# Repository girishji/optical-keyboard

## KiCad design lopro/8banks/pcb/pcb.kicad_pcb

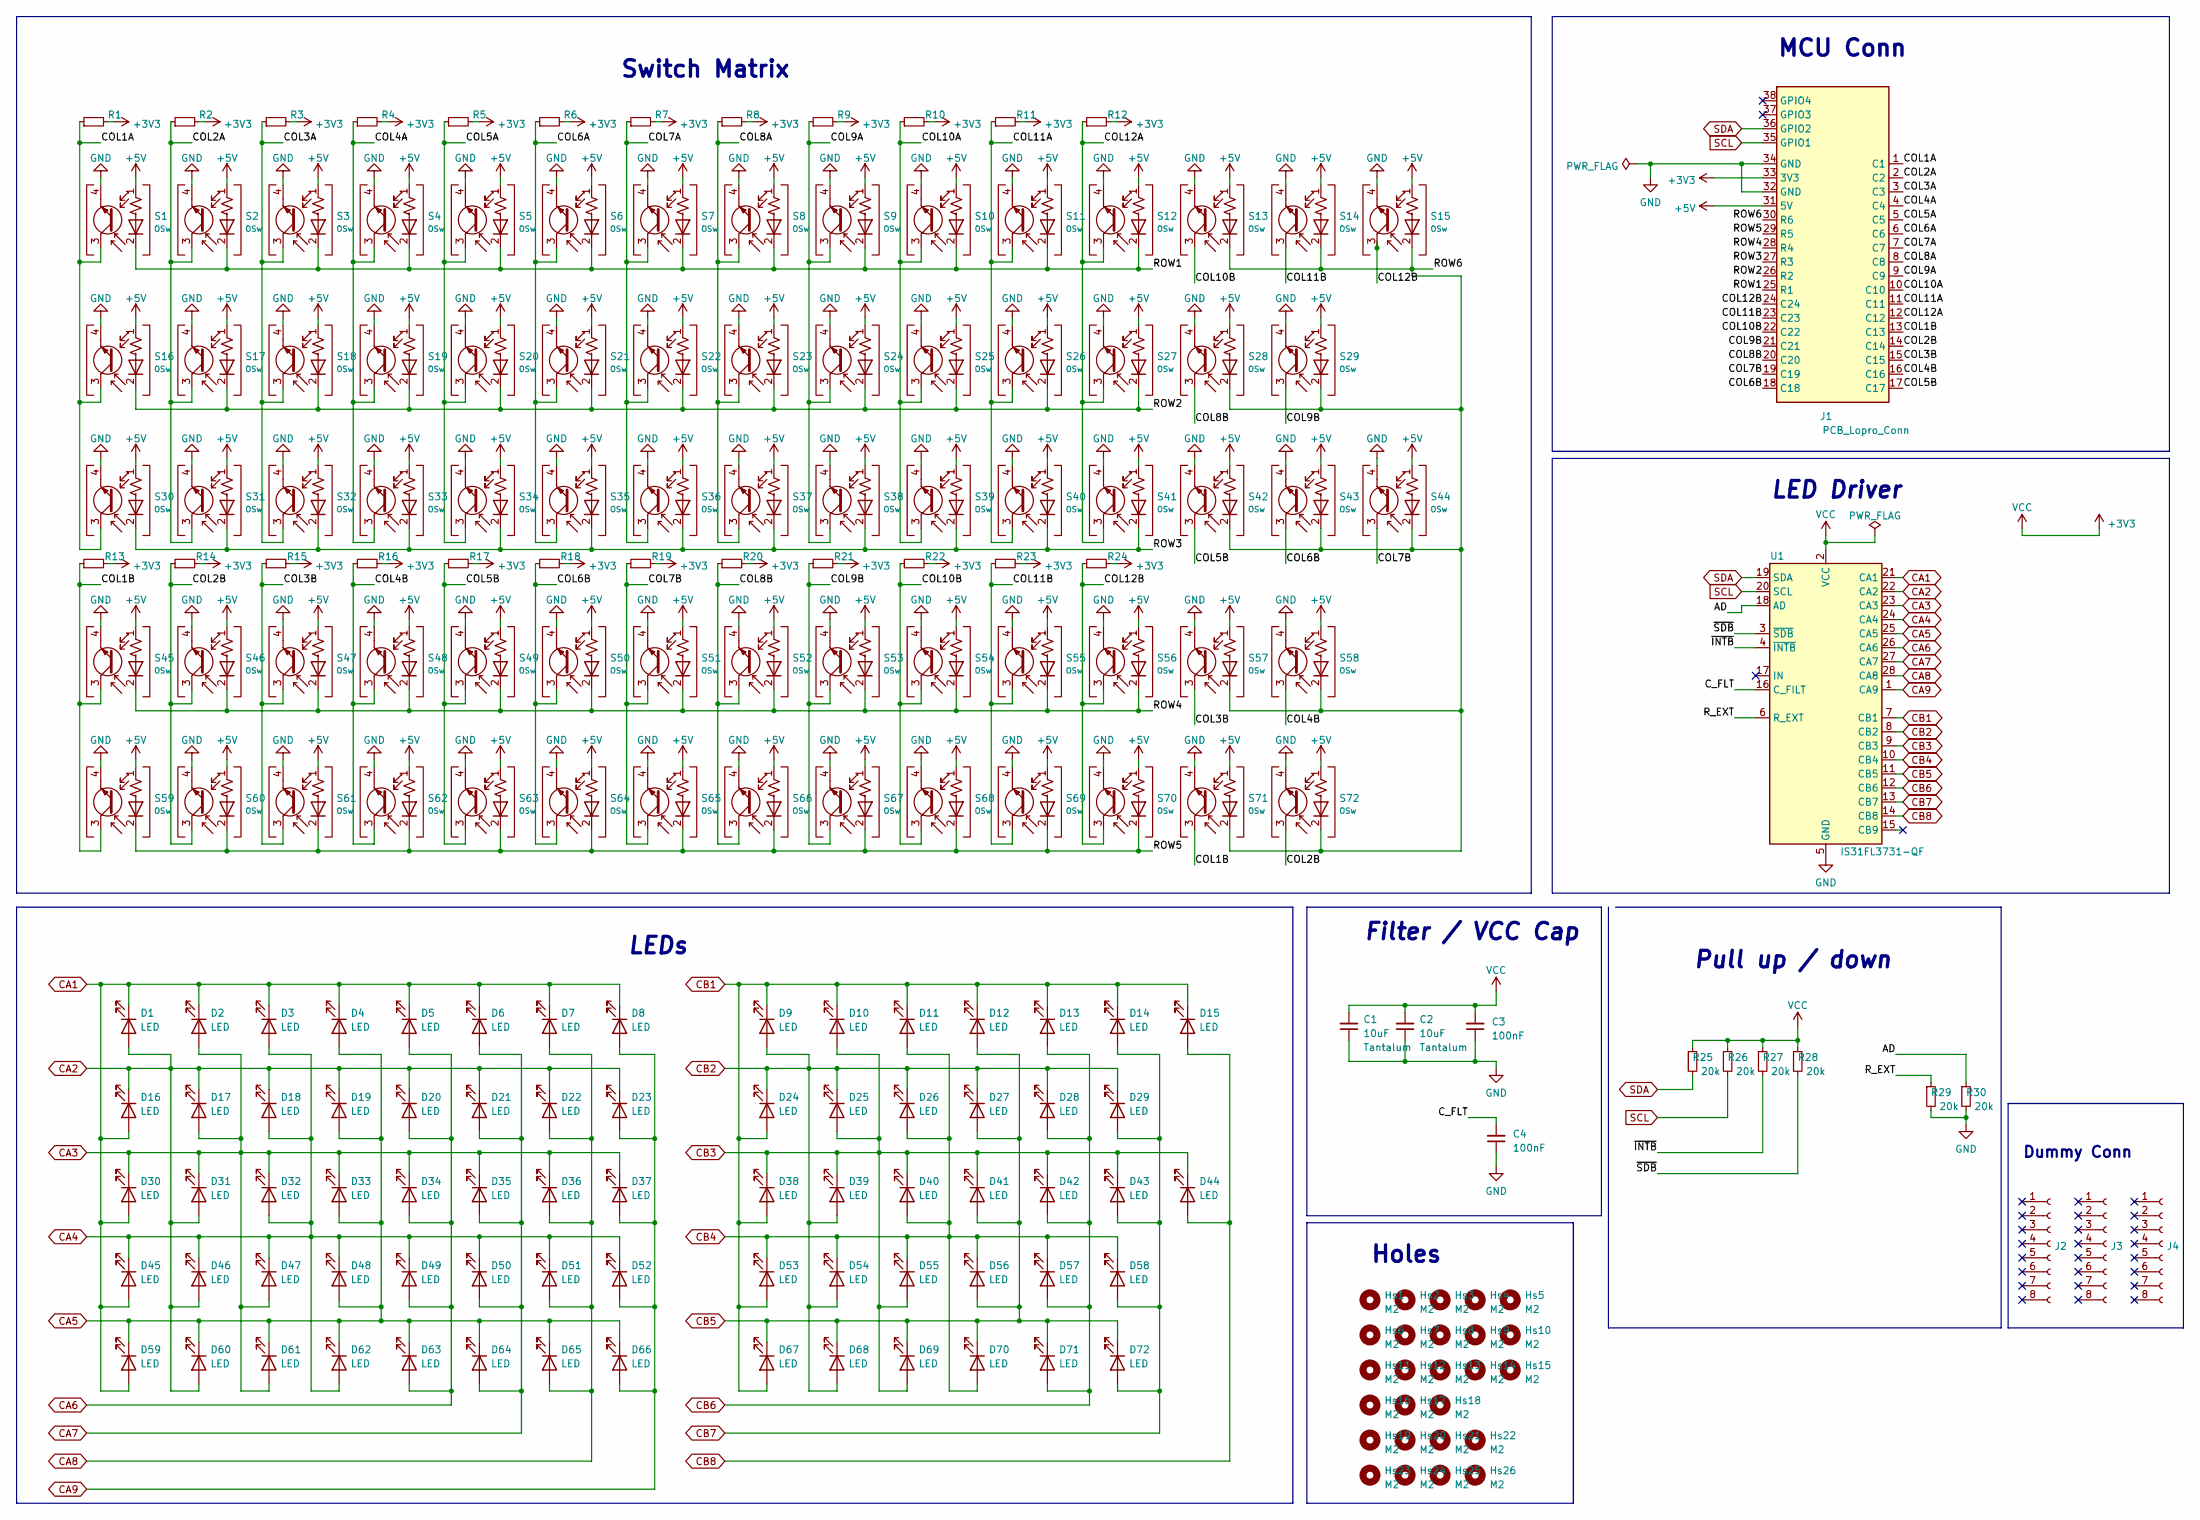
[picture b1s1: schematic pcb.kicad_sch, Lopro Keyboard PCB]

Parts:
C1, C2: 10uF; C_1206_3216Metric; JLC 10uF_tantalum
C3, C4: 100nF; C_0603_1608Metric; JLC smd_100nf
D1, D2, D3, D4, D5, D6, D7, D8, D9, D10, D11, D12, D13, D14, D15, D16, D17, D18, D19, D20, D21, D22, D23, D24, D25, D26, D27, D28, D29, D30, D31, D32, D33, D34, D35, D36, D37, D38, D39, D40, D41, D42, D43, D44, D45, D46, D47, D48, D49, D50, D51, D52, D53, D54, D55, D56, D57, D58, D59, D60, D61, D62, D63, D64, D65, D66, D67, D68, D69, D70, D71, D72: LED; LED_0603_1608Metric_Pad1.05x0.95mm_HandSolder
Hs1, Hs2, Hs3, Hs4, Hs5, Hs6, Hs7, Hs8, Hs9, Hs10, Hs11, Hs12, Hs13, Hs14, Hs15, Hs16, Hs17, Hs18, Hs19, Hs20, Hs21, Hs22, Hs23, Hs24, Hs25, Hs26: M2; SMTSO_M2
J1: PCB_Lopro_Conn; DSUB-37_Female_Horizontal_P2.77x2.84mm_EdgePinOffset4.94mm_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
J2, J3, J4: Conn_01x08_Female; PinHeader_1x08_P2.54mm_Vertical
R1, R2, R3, R4, R5, R6, R7, R8, R9, R10, R11, R12, R13, R14, R15, R16, R17, R18, R19, R20, R21, R22, R23, R24: R_Small; R_0603_1608Metric_Pad0.98x0.95mm_HandSolder
R25, R26, R27, R28, R29, R30: 20k; R_0603_1608Metric; JLC 20k
S1, S2, S3, S4, S5, S6, S7, S8, S9, S10, S11, S12, S13, S14, S15, S16, S17, S18, S19, S20, S21, S22, S23, S24, S25, S26, S27, S28, S29, S30, S31, S32, S33, S34, S35, S36, S37, S38, S39, S40, S41, S42, S43, S44, S45, S46, S47, S48, S49, S50, S51, S52, S53, S54, S55, S56, S57, S58, S59, S60, S61, S62, S63, S64, S65, S66, S67, S68, S69, S70, S71, S72: OSw; Keychron_Optical_Switch_1u
U1: IS31FL3731-QF; QFN-28-1EP_4x4mm_P0.4mm_EP2.3x2.3mm; JLCPCB IS31FL3731-QFLS2-TR

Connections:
+3V3: C1.2, C2.2, C3.2, J1.33 (3V3), R1.2, R2.2, R3.2, R4.2, R5.2, R6.2, R7.2, R8.2, R9.2, R10.2, R11.2, R12.2, R13.2, R14.2, R15.2, R16.2, R17.2, R18.2, R19.2, R20.2, R21.2, R22.2, R23.2, R24.2, R25.1, R26.1, R27.1, R28.1, U1.2 (VCC)
+5V: J1.31 (5V), S1.1 (IR_A), S2.1 (IR_A), S3.1 (IR_A), S4.1 (IR_A), S5.1 (IR_A), S6.1 (IR_A), S7.1 (IR_A), S8.1 (IR_A), S9.1 (IR_A), S10.1 (IR_A), S11.1 (IR_A), S12.1 (IR_A), S13.1 (IR_A), S14.1 (IR_A), S15.1 (IR_A), S16.1 (IR_A), S17.1 (IR_A), S18.1 (IR_A), S19.1 (IR_A), S20.1 (IR_A), S21.1 (IR_A), S22.1 (IR_A), S23.1 (IR_A), S24.1 (IR_A), S25.1 (IR_A), S26.1 (IR_A), S27.1 (IR_A), S28.1 (IR_A), S29.1 (IR_A), S30.1 (IR_A), S31.1 (IR_A), S32.1 (IR_A), S33.1 (IR_A), S34.1 (IR_A), S35.1 (IR_A), S36.1 (IR_A), S37.1 (IR_A), S38.1 (IR_A), S39.1 (IR_A), S40.1 (IR_A), S41.1 (IR_A), S42.1 (IR_A), S43.1 (IR_A), S44.1 (IR_A), S45.1 (IR_A), S46.1 (IR_A), S47.1 (IR_A), S48.1 (IR_A), S49.1 (IR_A), S50.1 (IR_A), S51.1 (IR_A), S52.1 (IR_A), S53.1 (IR_A), S54.1 (IR_A), S55.1 (IR_A), S56.1 (IR_A), S57.1 (IR_A), S58.1 (IR_A), S59.1 (IR_A), S60.1 (IR_A), S61.1 (IR_A), S62.1 (IR_A), S63.1 (IR_A), S64.1 (IR_A), S65.1 (IR_A), S66.1 (IR_A), S67.1 (IR_A), S68.1 (IR_A), S69.1 (IR_A), S70.1 (IR_A), S71.1 (IR_A), S72.1 (IR_A)
/AD: R30.1, U1.18 (AD)
/COL1A: J1.1 (C1), R1.1, S1.3 (C), S16.3 (C), S30.3 (C)
/COL1B: J1.13 (C13), R13.1, S45.3 (C), S59.3 (C), S71.3 (C)
/COL2A: J1.2 (C2), R2.1, S2.3 (C), S17.3 (C), S31.3 (C)
/COL2B: J1.14 (C14), R14.1, S46.3 (C), S60.3 (C), S72.3 (C)
/COL3A: J1.3 (C3), R3.1, S3.3 (C), S18.3 (C), S32.3 (C)
/COL3B: J1.15 (C15), R15.1, S47.3 (C), S57.3 (C), S61.3 (C)
/COL4A: J1.4 (C4), R4.1, S4.3 (C), S19.3 (C), S33.3 (C)
/COL4B: J1.16 (C16), R16.1, S48.3 (C), S58.3 (C), S62.3 (C)
/COL5A: J1.5 (C5), R5.1, S5.3 (C), S20.3 (C), S34.3 (C)
/COL5B: J1.17 (C17), R17.1, S42.3 (C), S49.3 (C), S63.3 (C)
/COL6A: J1.6 (C6), R6.1, S6.3 (C), S21.3 (C), S35.3 (C)
/COL6B: J1.18 (C18), R18.1, S43.3 (C), S50.3 (C), S64.3 (C)
/COL7A: J1.7 (C7), R7.1, S7.3 (C), S22.3 (C), S36.3 (C)
/COL7B: J1.19 (C19), R19.1, S44.3 (C), S51.3 (C), S65.3 (C)
/COL8A: J1.8 (C8), R8.1, S8.3 (C), S23.3 (C), S37.3 (C)
/COL8B: J1.20 (C20), R20.1, S28.3 (C), S52.3 (C), S66.3 (C)
/COL9A: J1.9 (C9), R9.1, S9.3 (C), S24.3 (C), S38.3 (C)
/COL9B: J1.21 (C21), R21.1, S29.3 (C), S53.3 (C), S67.3 (C)
/COL10A: J1.10 (C10), R10.1, S10.3 (C), S25.3 (C), S39.3 (C)
/COL10B: J1.22 (C22), R22.1, S13.3 (C), S54.3 (C), S68.3 (C)
/COL11A: J1.11 (C11), R11.1, S11.3 (C), S26.3 (C), S40.3 (C)
/COL11B: J1.23 (C23), R23.1, S14.3 (C), S55.3 (C), S69.3 (C)
/COL12A: J1.12 (C12), R12.1, S12.3 (C), S27.3 (C), S41.3 (C)
/COL12B: J1.24 (C24), R24.1, S15.3 (C), S56.3 (C), S70.3 (C)
/C_FLT: C4.2, U1.16 (C_FILT)
/ROW1: J1.25 (R1), S1.2 (IR_K), S2.2 (IR_K), S3.2 (IR_K), S4.2 (IR_K), S5.2 (IR_K), S6.2 (IR_K), S7.2 (IR_K), S8.2 (IR_K), S9.2 (IR_K), S10.2 (IR_K), S11.2 (IR_K), S12.2 (IR_K)
/ROW2: J1.26 (R2), S16.2 (IR_K), S17.2 (IR_K), S18.2 (IR_K), S19.2 (IR_K), S20.2 (IR_K), S21.2 (IR_K), S22.2 (IR_K), S23.2 (IR_K), S24.2 (IR_K), S25.2 (IR_K), S26.2 (IR_K), S27.2 (IR_K)
/ROW3: J1.27 (R3), S30.2 (IR_K), S31.2 (IR_K), S32.2 (IR_K), S33.2 (IR_K), S34.2 (IR_K), S35.2 (IR_K), S36.2 (IR_K), S37.2 (IR_K), S38.2 (IR_K), S39.2 (IR_K), S40.2 (IR_K), S41.2 (IR_K)
/ROW4: J1.28 (R4), S45.2 (IR_K), S46.2 (IR_K), S47.2 (IR_K), S48.2 (IR_K), S49.2 (IR_K), S50.2 (IR_K), S51.2 (IR_K), S52.2 (IR_K), S53.2 (IR_K), S54.2 (IR_K), S55.2 (IR_K), S56.2 (IR_K)
/ROW5: J1.29 (R5), S59.2 (IR_K), S60.2 (IR_K), S61.2 (IR_K), S62.2 (IR_K), S63.2 (IR_K), S64.2 (IR_K), S65.2 (IR_K), S66.2 (IR_K), S67.2 (IR_K), S68.2 (IR_K), S69.2 (IR_K), S70.2 (IR_K)
/ROW6: J1.30 (R6), S13.2 (IR_K), S14.2 (IR_K), S15.2 (IR_K), S28.2 (IR_K), S29.2 (IR_K), S42.2 (IR_K), S43.2 (IR_K), S44.2 (IR_K), S57.2 (IR_K), S58.2 (IR_K), S71.2 (IR_K), S72.2 (IR_K)
/R_EXT: R29.1, U1.6 (R_EXT)
/~INTB: R27.2, U1.4 (~INTB)
/~SDB: R28.2, U1.3 (~SDB)
CA1: D1.1 (K), D2.1 (K), D3.1 (K), D4.1 (K), D5.1 (K), D6.1 (K), D7.1 (K), D8.1 (K), D16.2 (A), D30.2 (A), D45.2 (A), D59.2 (A), U1.21 (CA1)
CA2: D1.2 (A), D16.1 (K), D17.1 (K), D18.1 (K), D19.1 (K), D20.1 (K), D21.1 (K), D22.1 (K), D23.1 (K), D31.2 (A), D46.2 (A), D60.2 (A), U1.22 (CA2)
CA3: D2.2 (A), D17.2 (A), D30.1 (K), D31.1 (K), D32.1 (K), D33.1 (K), D34.1 (K), D35.1 (K), D36.1 (K), D37.1 (K), D47.2 (A), D61.2 (A), U1.23 (CA3)
CA4: D3.2 (A), D18.2 (A), D32.2 (A), D45.1 (K), D46.1 (K), D47.1 (K), D48.1 (K), D49.1 (K), D50.1 (K), D51.1 (K), D52.1 (K), D62.2 (A), U1.24 (CA4)
CA5: D4.2 (A), D19.2 (A), D33.2 (A), D48.2 (A), D59.1 (K), D60.1 (K), D61.1 (K), D62.1 (K), D63.1 (K), D64.1 (K), D65.1 (K), D66.1 (K), U1.25 (CA5)
CA6: D5.2 (A), D20.2 (A), D34.2 (A), D49.2 (A), D63.2 (A), U1.26 (CA6)
CA7: D6.2 (A), D21.2 (A), D35.2 (A), D50.2 (A), D64.2 (A), U1.27 (CA7)
CA8: D7.2 (A), D22.2 (A), D36.2 (A), D51.2 (A), D65.2 (A), U1.28 (CA8)
CA9: D8.2 (A), D23.2 (A), D37.2 (A), D52.2 (A), D66.2 (A), U1.1 (CA9)
CB1: D9.1 (K), D10.1 (K), D11.1 (K), D12.1 (K), D13.1 (K), D14.1 (K), D15.1 (K), D24.2 (A), D38.2 (A), D53.2 (A), D67.2 (A), U1.7 (CB1)
CB2: D9.2 (A), D24.1 (K), D25.1 (K), D26.1 (K), D27.1 (K), D28.1 (K), D29.1 (K), D39.2 (A), D54.2 (A), D68.2 (A), U1.8 (CB2)
CB3: D10.2 (A), D25.2 (A), D38.1 (K), D39.1 (K), D40.1 (K), D41.1 (K), D42.1 (K), D43.1 (K), D44.1 (K), D55.2 (A), D69.2 (A), U1.9 (CB3)
CB4: D11.2 (A), D26.2 (A), D40.2 (A), D53.1 (K), D54.1 (K), D55.1 (K), D56.1 (K), D57.1 (K), D58.1 (K), D70.2 (A), U1.10 (CB4)
CB5: D12.2 (A), D27.2 (A), D41.2 (A), D56.2 (A), D67.1 (K), D68.1 (K), D69.1 (K), D70.1 (K), D71.1 (K), D72.1 (K), U1.11 (CB5)
CB6: D13.2 (A), D28.2 (A), D42.2 (A), D57.2 (A), D71.2 (A), U1.12 (CB6)
CB7: D14.2 (A), D29.2 (A), D43.2 (A), D58.2 (A), D72.2 (A), U1.13 (CB7)
CB8: D15.2 (A), D44.2 (A), U1.14 (CB8)
GND: C1.1, C2.1, C3.1, C4.1, J1.32 (GND), J1.34 (GND), R29.2, R30.2, S1.4 (E), S2.4 (E), S3.4 (E), S4.4 (E), S5.4 (E), S6.4 (E), S7.4 (E), S8.4 (E), S9.4 (E), S10.4 (E), S11.4 (E), S12.4 (E), S13.4 (E), S14.4 (E), S15.4 (E), S16.4 (E), S17.4 (E), S18.4 (E), S19.4 (E), S20.4 (E), S21.4 (E), S22.4 (E), S23.4 (E), S24.4 (E), S25.4 (E), S26.4 (E), S27.4 (E), S28.4 (E), S29.4 (E), S30.4 (E), S31.4 (E), S32.4 (E), S33.4 (E), S34.4 (E), S35.4 (E), S36.4 (E), S37.4 (E), S38.4 (E), S39.4 (E), S40.4 (E), S41.4 (E), S42.4 (E), S43.4 (E), S44.4 (E), S45.4 (E), S46.4 (E), S47.4 (E), S48.4 (E), S49.4 (E), S50.4 (E), S51.4 (E), S52.4 (E), S53.4 (E), S54.4 (E), S55.4 (E), S56.4 (E), S57.4 (E), S58.4 (E), S59.4 (E), S60.4 (E), S61.4 (E), S62.4 (E), S63.4 (E), S64.4 (E), S65.4 (E), S66.4 (E), S67.4 (E), S68.4 (E), S69.4 (E), S70.4 (E), S71.4 (E), S72.4 (E), U1.5 (GND), U1.29 (GND)
SCL: J1.35 (GPIO1), R26.2, U1.20 (SCL)
SDA: J1.36 (GPIO2), R25.2, U1.19 (SDA)

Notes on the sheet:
Holes
LED Driver
LEDs
Switch Matrix
Dummy Conn
Pull up / down
Filter / VCC Cap
MCU Conn

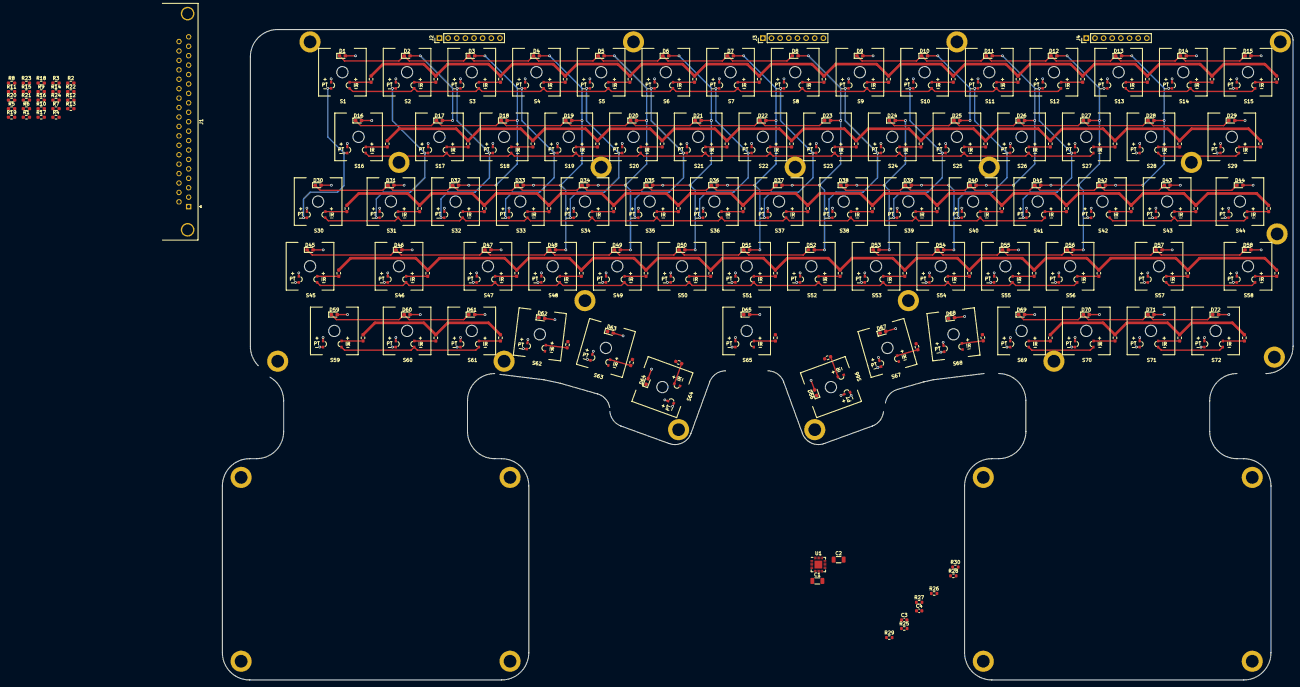
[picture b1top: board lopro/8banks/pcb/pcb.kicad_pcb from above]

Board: 2 copper layers, 314.5 x 191.1 mm, 209 parts (0 on the bottom side), 57 nets.

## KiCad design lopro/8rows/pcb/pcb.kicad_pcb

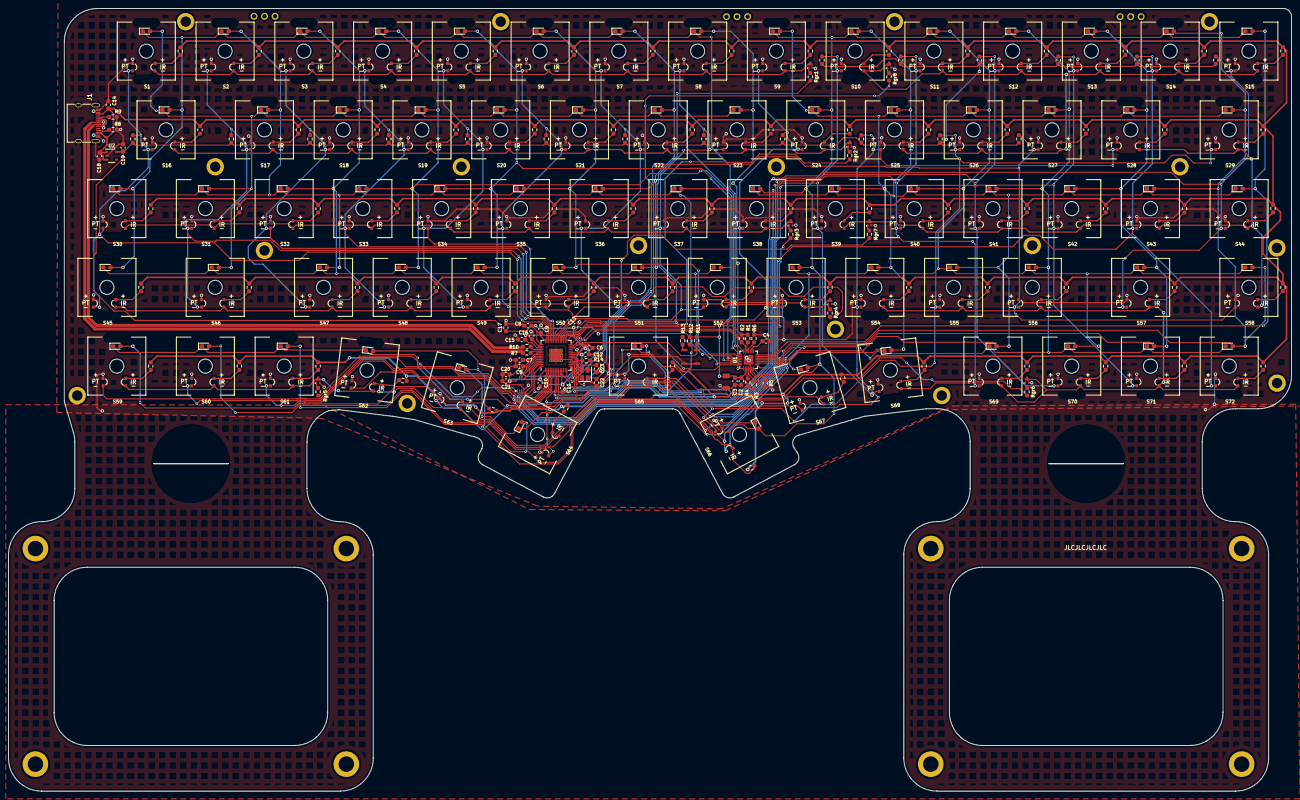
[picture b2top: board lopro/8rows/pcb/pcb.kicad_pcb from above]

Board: 2 copper layers, 309.5 x 188.8 mm, 324 parts (0 on the bottom side), 159 nets.

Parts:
C1: 10uF; C_1206_3216Metric
C2, C17: 10uF; C_0603_1608Metric_Pad1.08x0.95mm_HandSolder
C3, C4, C5, C6, C7, C8, C9, C10, C11, C12, C13, C20: 100nF; C_0603_1608Metric_Pad1.08x0.95mm_HandSolder
C14, C18, C21: 2.2uF; C_0603_1608Metric_Pad1.08x0.95mm_HandSolder
C15, C16, C19: 1uF; C_0603_1608Metric_Pad1.08x0.95mm_HandSolder
C22, C23: 15pF; C_0603_1608Metric_Pad1.08x0.95mm_HandSolder
D1, D2, D3, D4, D5, D6, D7, D8, D9, D10, D11, D12, D13, D14, D15, D16, D17, D18, D19, D20, D21, D22, D23, D24, D25, D26, D27, D28, D29, D30, D31, D32, D33, D34, D35, D36, D37, D38, D39, D40, D41, D42, D43, D44, D45, D46, D47, D48, D49, D50, D51, D52, D53, D54, D55, D56, D57, D58, D59, D60, D61, D62, D63, D64, D65, D66, D67, D68, D69, D70, D71, D72: LED; LED_0603_1608Metric_Pad1.05x0.95mm_HandSolder
Hs1, Hs2, Hs3, Hs4, Hs5, Hs6, Hs7, Hs8, Hs9, Hs10, Hs11, Hs12, Hs13, Hs14, Hs15, Hs16, Hs17: M1.6; SMTSO_M1.6
Hs18, Hs19, Hs20, Hs21, Hs22, Hs23, Hs24, Hs25: M2; SMTSO_M2
J1: U262-161N-4BVC11; USB_C_Receptacle_XKB_U262-16XN-4BVC11
J2, J3, J4: Conn_01x03; PinHeader_1x03_P2.54mm_Vertical
JLC1: JLC_Order_Num
Q1, Q2, Q3, Q4, Q5, Q6, Q7, Q8: Q_NMOS_DGS; Diodes_U_DFN1212_3_Handsolder
R1, R2, R3: 4.7k; R_0603_1608Metric_Pad0.98x0.95mm_HandSolder
R4, R5, R6: 20k; R_0603_1608Metric_Pad0.98x0.95mm_HandSolder
R7, R10: 27R; R_0603_1608Metric_Pad0.98x0.95mm_HandSolder
R8, R9: 5.1k; R_0603_1608Metric_Pad0.98x0.95mm_HandSolder
R11, R12: 10k; R_0603_1608Metric_Pad0.98x0.95mm_HandSolder
R13, R14: 1k; R_0603_1608Metric_Pad0.98x0.95mm_HandSolder
Rgr1, Rgr2, Rgr3, Rgr4, Rgr5, Rgr6, Rgr7, Rgr8: 160R; R_0603_1608Metric_Pad0.98x0.95mm_HandSolder
Ri1, Ri2, Ri3, Ri4, Ri5, Ri6, Ri7, Ri8, Ri9, Ri10, Ri11, Ri12, Ri13, Ri14, Ri15, Ri16, Ri17, Ri18, Ri19, Ri20, Ri21, Ri22, Ri23, Ri24, Ri25, Ri26, Ri27, Ri28, Ri29, Ri30, Ri31, Ri32, Ri33, Ri34, Ri35, Ri36, Ri37, Ri38, Ri39, Ri40, Ri41, Ri42, Ri43, Ri44, Ri45, Ri46, Ri47, Ri48, Ri49, Ri50, Ri51, Ri52, Ri53, Ri54, Ri55, Ri56, Ri57, Ri58, Ri59, Ri60, Ri61, Ri62, Ri63, Ri64, Ri65, Ri66, Ri67, Ri68, Ri69, Ri70, Ri71, Ri72: R_IR; R_0603_1608Metric_Pad0.98x0.95mm_HandSolder
Rpt1, Rpt2, Rpt3, Rpt4, Rpt5, Rpt6, Rpt7, Rpt8, Rpt9, Rpt10, Rpt11, Rpt12, Rpt13, Rpt14, Rpt15, Rpt16, Rpt17, Rpt18: Rpt; R_0603_1608Metric_Pad0.98x0.95mm_HandSolder
S1, S2, S3, S4, S5, S6, S7, S8, S9, S10, S11, S12, S13, S14, S15, S16, S17, S18, S19, S20, S21, S22, S23, S24, S25, S26, S27, S28, S29, S30, S31, S32, S33, S34, S35, S36, S37, S38, S39, S40, S41, S42, S43, S44, S45, S46, S47, S48, S49, S50, S51, S52, S53, S54, S55, S56, S57, S58, S59, S60, S61, S62, S63, S64, S65, S66, S67, S68, S69, S70, S71, S72: OSw; Keychron_Optical_Switch_1u
SW1, SW2: SW_DIP_x01_XKB_TS_2030; SW_CK_KXT3
U1: IS31FL3731-QF; QFN-28-1EP_4x4mm_P0.4mm_EP2.3x2.3mm-Handsolder
U2: NCP114ASN330T1G; TSOP-5_1.65x3.05mm_P0.95mm
U3: RP2040; RP2040-QFN-56-Handsolder
U4: Memory_Flash_W25Q64_XSON; 8-USON-Handsolder
X1: 12.000MHz; Crystal_SMD_2520-4Pin_2.5x2.0mm-Handsolder

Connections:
+1V1: C5.1, C6.1, C15.1, U3.23 (DVDD), U3.45 (VREG_VOUT), U3.50 (DVDD)
+3V3: C1.2, C2.1, C3.1, C7.1, C8.1, C9.1, C10.1, C11.1, C12.1, C13.1, C16.1, C17.1, C19.1, C20.1, C21.1, R1.1, R2.1, R3.1, R4.1, R11.1, R12.1, Rpt1.2, Rpt2.2, Rpt3.2, Rpt4.2, Rpt5.2, Rpt6.2, Rpt7.2, Rpt8.2, Rpt9.2, Rpt10.2, Rpt11.2, Rpt12.2, Rpt13.2, Rpt14.2, Rpt15.2, Rpt16.2, Rpt17.2, Rpt18.2, U1.2 (VCC), U2.5 (VOUT), U3.1 (IOVDD), U3.10 (IOVDD), U3.22 (IOVDD), U3.33 (IOVDD), U3.42 (IOVDD), U3.43 (ADC_AVDD), U3.44 (VREG_IN), U3.48 (USB_VDD), U3.49 (IOVDD), U4.8 (VCC)
+5V: C14.2, C18.1, J1.A4 (VBUS), J1.A9 (VBUS), J1.B4 (VBUS), J1.B9 (VBUS), Ri1.1, Ri2.1, Ri3.1, Ri4.1, Ri5.1, Ri6.1, Ri7.1, Ri8.1, Ri9.1, Ri10.1, Ri11.1, Ri12.1, Ri13.1, Ri14.1, Ri15.1, Ri16.1, Ri17.1, Ri18.1, Ri19.1, Ri20.1, Ri21.1, Ri22.1, Ri23.1, Ri24.1, Ri25.1, Ri26.1, Ri27.1, Ri28.1, Ri29.1, Ri30.1, Ri31.1, Ri32.1, Ri33.1, Ri34.1, Ri35.1, Ri36.1, Ri37.1, Ri38.1, Ri39.1, Ri40.1, Ri41.1, Ri42.1, Ri43.1, Ri44.1, Ri45.1, Ri46.1, Ri47.1, Ri48.1, Ri49.1, Ri50.1, Ri51.1, Ri52.1, Ri53.1, Ri54.1, Ri55.1, Ri56.1, Ri57.1, Ri58.1, Ri59.1, Ri60.1, Ri61.1, Ri62.1, Ri63.1, Ri64.1, Ri65.1, Ri66.1, Ri67.1, Ri68.1, Ri69.1, Ri70.1, Ri71.1, Ri72.1, U2.1 (IN), U2.3 (EN)
/AD: R6.1, U1.18 (AD)
/COL1A: Rpt1.1, S1.3 (C), S16.3 (C), S30.3 (C), S45.3 (C), U3.41 (GPIO29_ADC3)
/COL1B: Rpt10.1, S10.3 (C), S39.3 (C), S59.3 (C), S68.3 (C), U3.2 (GPIO0)
/COL2A: Rpt2.1, S2.3 (C), S17.3 (C), S31.3 (C), S46.3 (C), U3.40 (GPIO28_ADC2)
/COL2B: Rpt11.1, S11.3 (C), S40.3 (C), S60.3 (C), S69.3 (C), U3.3 (GPIO1)
/COL3A: Rpt3.1, S3.3 (C), S18.3 (C), S32.3 (C), S47.3 (C), U3.39 (GPIO27_ADC1)
/COL3B: Rpt12.1, S12.3 (C), S41.3 (C), S61.3 (C), S70.3 (C), U3.4 (GPIO2)
/COL4A: Rpt4.1, S4.3 (C), S19.3 (C), S33.3 (C), S48.3 (C), U3.38 (GPIO26_ADC0)
/COL4B: Rpt13.1, S13.3 (C), S42.3 (C), S62.3 (C), S71.3 (C), U3.5 (GPIO3)
/COL5A: Rpt5.1, S5.3 (C), S20.3 (C), S34.3 (C), S49.3 (C), U3.37 (GPIO25)
/COL5B: Rpt14.1, S14.3 (C), S43.3 (C), S63.3 (C), S72.3 (C), U3.6 (GPIO4)
/COL6A: Rpt6.1, S6.3 (C), S21.3 (C), S35.3 (C), S50.3 (C), U3.36 (GPIO24)
/COL6B: Rpt15.1, S15.3 (C), S44.3 (C), S57.3 (C), S64.3 (C), U3.7 (GPIO5)
/COL7A: Rpt7.1, S7.3 (C), S22.3 (C), S36.3 (C), S51.3 (C), U3.35 (GPIO23)
/COL7B: Rpt16.1, S27.3 (C), S56.3 (C), S58.3 (C), S65.3 (C), U3.8 (GPIO6)
/COL8A: Rpt8.1, S8.3 (C), S23.3 (C), S37.3 (C), S52.3 (C), U3.34 (GPIO22)
/COL8B: Rpt17.1, S26.3 (C), S29.3 (C), S55.3 (C), S66.3 (C), U3.9 (GPIO7)
/COL9A: Rpt9.1, S9.3 (C), S24.3 (C), S38.3 (C), S53.3 (C), U3.32 (GPIO21)
/COL9B: Rpt18.1, S25.3 (C), S28.3 (C), S54.3 (C), S67.3 (C), U3.11 (GPIO8)
/C_FLT: C4.1, U1.16 (C_FILT)
/P1: Rgr1.1, U3.31 (GPIO20)
/P2: Rgr2.1, U3.30 (GPIO19)
/P3: Rgr3.1, U3.29 (GPIO18)
/P4: Rgr4.1, U3.18 (GPIO15)
/P5: Rgr5.1, U3.17 (GPIO14)
/P6: Rgr6.1, U3.16 (GPIO13)
/P7: Rgr7.1, U3.15 (GPIO12)
/P8: Rgr8.1, U3.14 (GPIO11)
/QSPI_SCLK: U3.52 (QSPI_SCLK), U4.6 (CLK)
/QSPI_SD0: U3.53 (QSPI_SD0), U4.5 (DI_(IO0))
/QSPI_SD1: U3.55 (QSPI_SD1), U4.2 (DO_(IO1))
/QSPI_SD2: U3.54 (QSPI_SD2), U4.3 (~WP_(IO2))
/QSPI_SD3: U3.51 (QSPI_SD3), U4.7 (~HOLD_(IO3))
/QSPI_SS: R12.2, R13.1, U3.56 (QSPI_SS), U4.1 (~{CS)
/ROW1: Q1.1 (D), S1.2 (IR_K), S2.2 (IR_K), S3.2 (IR_K), S4.2 (IR_K), S5.2 (IR_K), S6.2 (IR_K), S7.2 (IR_K), S8.2 (IR_K), S9.2 (IR_K)
/ROW2: Q2.1 (D), S16.2 (IR_K), S17.2 (IR_K), S18.2 (IR_K), S19.2 (IR_K), S20.2 (IR_K), S21.2 (IR_K), S22.2 (IR_K), S23.2 (IR_K), S24.2 (IR_K)
/ROW3: Q3.1 (D), S30.2 (IR_K), S31.2 (IR_K), S32.2 (IR_K), S33.2 (IR_K), S34.2 (IR_K), S35.2 (IR_K), S36.2 (IR_K), S37.2 (IR_K), S38.2 (IR_K)
/ROW4: Q4.1 (D), S45.2 (IR_K), S46.2 (IR_K), S47.2 (IR_K), S48.2 (IR_K), S49.2 (IR_K), S50.2 (IR_K), S51.2 (IR_K), S52.2 (IR_K), S53.2 (IR_K)
/ROW5: Q5.1 (D), S59.2 (IR_K), S60.2 (IR_K), S61.2 (IR_K), S62.2 (IR_K), S63.2 (IR_K), S64.2 (IR_K), S65.2 (IR_K), S66.2 (IR_K), S67.2 (IR_K)
/ROW6: Q6.1 (D), S54.2 (IR_K), S55.2 (IR_K), S56.2 (IR_K), S57.2 (IR_K), S68.2 (IR_K), S69.2 (IR_K), S70.2 (IR_K), S71.2 (IR_K), S72.2 (IR_K)
/ROW7: Q7.1 (D), S28.2 (IR_K), S29.2 (IR_K), S39.2 (IR_K), S40.2 (IR_K), S41.2 (IR_K), S42.2 (IR_K), S43.2 (IR_K), S44.2 (IR_K), S58.2 (IR_K)
/ROW8: Q8.1 (D), S10.2 (IR_K), S11.2 (IR_K), S12.2 (IR_K), S13.2 (IR_K), S14.2 (IR_K), S15.2 (IR_K), S25.2 (IR_K), S26.2 (IR_K), S27.2 (IR_K)
/RUN: R11.2, SW1.2, U3.26 (RUN)
/R_EXT: R5.1, U1.6 (R_EXT)
/USB_D+: J1.A6 (D1+), J1.B6 (D2+), R7.2
/USB_D-: J1.A7 (D1-), J1.B7 (D2-), R10.2
/XIN: C23.1, U3.20 (XIN), X1.3
/XOUT: R14.1, U3.21 (XOUT)
/~INTB: R3.2, U1.4 (~INTB)
/~SDB: R4.2, U1.3 (~SDB)
/~USB_BOOT: R13.2, SW2.2
CA1: D1.1 (K), D2.1 (K), D3.1 (K), D4.1 (K), D5.1 (K), D6.1 (K), D7.1 (K), D8.1 (K), D16.2 (A), D30.2 (A), D45.2 (A), U1.21 (CA1)
CA2: D1.2 (A), D16.1 (K), D17.1 (K), D18.1 (K), D19.1 (K), D20.1 (K), D21.1 (K), D22.1 (K), D23.1 (K), D31.2 (A), D46.2 (A), U1.22 (CA2)
CA3: D2.2 (A), D17.2 (A), D30.1 (K), D31.1 (K), D32.1 (K), D33.1 (K), D34.1 (K), D35.1 (K), D36.1 (K), D37.1 (K), D47.2 (A), U1.23 (CA3)
CA4: D3.2 (A), D18.2 (A), D32.2 (A), D45.1 (K), D46.1 (K), D47.1 (K), D48.1 (K), D49.1 (K), D50.1 (K), D51.1 (K), D52.1 (K), U1.24 (CA4)
CA5: D4.2 (A), D19.2 (A), D33.2 (A), D48.2 (A), U1.25 (CA5)
CA6: D5.2 (A), D20.2 (A), D34.2 (A), D49.2 (A), U1.26 (CA6)
CA7: D6.2 (A), D21.2 (A), D35.2 (A), D50.2 (A), U1.27 (CA7)
CA8: D7.2 (A), D22.2 (A), D36.2 (A), D51.2 (A), U1.28 (CA8)
CA9: D8.2 (A), D23.2 (A), D37.2 (A), D52.2 (A), U1.1 (CA9)
CB1: D9.1 (K), D10.1 (K), D11.1 (K), D12.1 (K), D13.1 (K), D14.1 (K), D15.1 (K), D24.2 (A), D38.2 (A), D53.2 (A), D59.2 (A), D66.2 (A), D67.2 (A), U1.7 (CB1)
CB2: D9.2 (A), D24.1 (K), D25.1 (K), D26.1 (K), D27.1 (K), D28.1 (K), D29.1 (K), D39.2 (A), D54.2 (A), D60.2 (A), D65.2 (A), D68.2 (A), U1.8 (CB2)
CB3: D10.2 (A), D25.2 (A), D38.1 (K), D39.1 (K), D40.1 (K), D41.1 (K), D42.1 (K), D43.1 (K), D44.1 (K), D55.2 (A), D61.2 (A), D64.2 (A), D69.2 (A), U1.9 (CB3)
CB4: D11.2 (A), D26.2 (A), D40.2 (A), D53.1 (K), D54.1 (K), D55.1 (K), D56.1 (K), D57.1 (K), D58.1 (K), D62.2 (A), D63.2 (A), D70.2 (A), U1.10 (CB4)
CB5: D12.2 (A), D27.2 (A), D41.2 (A), D56.2 (A), D67.1 (K), D68.1 (K), D69.1 (K), D70.1 (K), D71.1 (K), D72.1 (K), U1.11 (CB5)
CB6: D13.2 (A), D28.2 (A), D42.2 (A), D57.2 (A), D63.1 (K), D64.1 (K), D65.1 (K), D66.1 (K), D71.2 (A), U1.12 (CB6)
CB7: D14.2 (A), D29.2 (A), D43.2 (A), D58.2 (A), D59.1 (K), D60.1 (K), D61.1 (K), D62.1 (K), D72.2 (A), U1.13 (CB7)
CB8: D15.2 (A), D44.2 (A), U1.14 (CB8)
GND: C1.1, C2.2, C3.2, C4.2, C5.2, C6.2, C7.2, C8.2, C9.2, C10.2, C11.2, C12.2, C13.2, C14.1, C15.2, C16.2, C17.2, C18.2, C19.2, C20.2, C21.2, C22.2, C23.2, J1.A1 (GND), J1.A12 (GND), J1.B1 (GND), J1.B12 (GND), J1.S1 (SHIELD), Q1.3 (S), Q2.3 (S), Q3.3 (S), Q4.3 (S), Q5.3 (S), Q6.3 (S), Q7.3 (S), Q8.3 (S), R5.2, R6.2, R8.2, R9.2, S1.4 (E), S2.4 (E), S3.4 (E), S4.4 (E), S5.4 (E), S6.4 (E), S7.4 (E), S8.4 (E), S9.4 (E), S10.4 (E), S11.4 (E), S12.4 (E), S13.4 (E), S14.4 (E), S15.4 (E), S16.4 (E), S17.4 (E), S18.4 (E), S19.4 (E), S20.4 (E), S21.4 (E), S22.4 (E), S23.4 (E), S24.4 (E), S25.4 (E), S26.4 (E), S27.4 (E), S28.4 (E), S29.4 (E), S30.4 (E), S31.4 (E), S32.4 (E), S33.4 (E), S34.4 (E), S35.4 (E), S36.4 (E), S37.4 (E), S38.4 (E), S39.4 (E), S40.4 (E), S41.4 (E), S42.4 (E), S43.4 (E), S44.4 (E), S45.4 (E), S46.4 (E), S47.4 (E), S48.4 (E), S49.4 (E), S50.4 (E), S51.4 (E), S52.4 (E), S53.4 (E), S54.4 (E), S55.4 (E), S56.4 (E), S57.4 (E), S58.4 (E), S59.4 (E), S60.4 (E), S61.4 (E), S62.4 (E), S63.4 (E), S64.4 (E), S65.4 (E), S66.4 (E), S67.4 (E), S68.4 (E), S69.4 (E), S70.4 (E), S71.4 (E), S72.4 (E), SW1.1, SW2.1, U1.5 (GND), U1.29 (GND), U2.2 (GND), U3.19 (TESTEN), U3.57 (GND), U4.4 (GND), U4.9 (EP), X1.2, X1.4
unnamed: C22.1, R14.2, X1.1
unnamed: J1.A5 (CC1), R9.1
unnamed: J1.B5 (CC2), R8.1
unnamed: Q1.2 (G), Rgr1.2
unnamed: Q2.2 (G), Rgr2.2
unnamed: Q3.2 (G), Rgr3.2
unnamed: Q4.2 (G), Rgr4.2
unnamed: Q5.2 (G), Rgr5.2
unnamed: Q6.2 (G), Rgr6.2
unnamed: Q7.2 (G), Rgr7.2
unnamed: Q8.2 (G), Rgr8.2
unnamed: R7.1, U3.47 (USB_DP)
unnamed: R10.1, U3.46 (USB_DM)
unnamed: Ri1.2, S1.1 (IR_A)
unnamed: Ri2.2, S2.1 (IR_A)
unnamed: Ri3.2, S3.1 (IR_A)
unnamed: Ri4.2, S4.1 (IR_A)
unnamed: Ri5.2, S5.1 (IR_A)
unnamed: Ri6.2, S6.1 (IR_A)
unnamed: Ri7.2, S7.1 (IR_A)
unnamed: Ri8.2, S8.1 (IR_A)
unnamed: Ri9.2, S9.1 (IR_A)
unnamed: Ri10.2, S10.1 (IR_A)
unnamed: Ri11.2, S11.1 (IR_A)
unnamed: Ri12.2, S12.1 (IR_A)
unnamed: Ri13.2, S13.1 (IR_A)
unnamed: Ri14.2, S14.1 (IR_A)
unnamed: Ri15.2, S15.1 (IR_A)
unnamed: Ri16.2, S16.1 (IR_A)
unnamed: Ri17.2, S17.1 (IR_A)
unnamed: Ri18.2, S18.1 (IR_A)
unnamed: Ri19.2, S19.1 (IR_A)
unnamed: Ri20.2, S20.1 (IR_A)
unnamed: Ri21.2, S21.1 (IR_A)
unnamed: Ri22.2, S22.1 (IR_A)
unnamed: Ri23.2, S23.1 (IR_A)
unnamed: Ri24.2, S24.1 (IR_A)
unnamed: Ri25.2, S25.1 (IR_A)
unnamed: Ri26.2, S26.1 (IR_A)
unnamed: Ri27.2, S27.1 (IR_A)
unnamed: Ri28.2, S28.1 (IR_A)
unnamed: Ri29.2, S29.1 (IR_A)
unnamed: Ri30.2, S30.1 (IR_A)
unnamed: Ri31.2, S31.1 (IR_A)
unnamed: Ri32.2, S32.1 (IR_A)
unnamed: Ri33.2, S33.1 (IR_A)
unnamed: Ri34.2, S34.1 (IR_A)
unnamed: Ri35.2, S35.1 (IR_A)
unnamed: Ri36.2, S36.1 (IR_A)
unnamed: Ri37.2, S37.1 (IR_A)
unnamed: Ri38.2, S38.1 (IR_A)
unnamed: Ri39.2, S39.1 (IR_A)
unnamed: Ri40.2, S40.1 (IR_A)
unnamed: Ri41.2, S41.1 (IR_A)
unnamed: Ri42.2, S42.1 (IR_A)
unnamed: Ri43.2, S43.1 (IR_A)
unnamed: Ri44.2, S44.1 (IR_A)
unnamed: Ri45.2, S45.1 (IR_A)
unnamed: Ri46.2, S46.1 (IR_A)
unnamed: Ri47.2, S47.1 (IR_A)
unnamed: Ri48.2, S48.1 (IR_A)
unnamed: Ri49.2, S49.1 (IR_A)
unnamed: Ri50.2, S50.1 (IR_A)
unnamed: Ri51.2, S51.1 (IR_A)
unnamed: Ri52.2, S52.1 (IR_A)
unnamed: Ri53.2, S53.1 (IR_A)
unnamed: Ri54.2, S54.1 (IR_A)
unnamed: Ri55.2, S55.1 (IR_A)
unnamed: Ri56.2, S56.1 (IR_A)
unnamed: Ri57.2, S57.1 (IR_A)
unnamed: Ri58.2, S58.1 (IR_A)
unnamed: Ri59.2, S59.1 (IR_A)
unnamed: Ri60.2, S60.1 (IR_A)
unnamed: Ri61.2, S61.1 (IR_A)
unnamed: Ri62.2, S62.1 (IR_A)
unnamed: Ri63.2, S63.1 (IR_A)
unnamed: Ri64.2, S64.1 (IR_A)
unnamed: Ri65.2, S65.1 (IR_A)
unnamed: Ri66.2, S66.1 (IR_A)
unnamed: Ri67.2, S67.1 (IR_A)
unnamed: Ri68.2, S68.1 (IR_A)
unnamed: Ri69.2, S69.1 (IR_A)
unnamed: Ri70.2, S70.1 (IR_A)
unnamed: Ri71.2, S71.1 (IR_A)
unnamed: Ri72.2, S72.1 (IR_A)
SCL: R2.2, U1.20 (SCL), U3.28 (GPIO17)
SDA: R1.2, U1.19 (SDA), U3.27 (GPIO16)
